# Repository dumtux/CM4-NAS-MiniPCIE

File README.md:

**Rapberry PI compute module 4 NAS PCB for using JLCPCB.com. (pre-test version)**

# General view of PCB based on processing gbr files on JLCPCB.com

Main purpose of design is to make NAS with more reliable SATA connection comparing to USB-to-SATA converters. SATA controllers can be connected through MiniPCIe slot. There are variety of cards in market, mainly my intend was to use this for 2 SATA (see picture below). This is half size card. Cards for 4 SATA with RAID controller also can be connected. 

**Design is made using nighly version of KiCAD 5.99.0**
**Please study Raspberry PI CM4 datasheet**

# Differential lines
*PCB was designed by a newcomer. All steps made are listed below. This section is very important and risky. Mistakes can be made.  90 R and 100R impedance differential lines are used.Calculations of differential lines are made using JLCPCB internal [calculator](https://cart.jlcpcb.com/impedanceCalculation)*

Results of calculation - [90R](https://raw.githubusercontent.com/olvint/CM4-NAS-MiniPCIE/main/PICS/JLCPCB%20Impedance%2090R.png) and [100R](https://raw.githubusercontent.com/olvint/CM4-NAS-MiniPCIE/main/PICS/JLCPCB%20Impedance%20100R.png)

Those results put in KiCAD.

JLC7628 [Stackup](https://cart.jlcpcb.com/impedance) used all settings transfered to [KiCAD stackup](https://raw.githubusercontent.com/olvint/CM4-NAS-MiniPCIE/main/PICS/KiCAD%20Stack.png)

All vias minimal diameter is 0.45 as price will be much higher for VIAs of less size.

# PCB description
## Sockets on PCB
- MiniPCIe slot (designed for hlaf-size cards)
- HDMI in order to use device as media player
- Gigabit LAN
- SD card slot for using CM4’s without eMMC
- USB A 2.0 socket for connecting periphery like Zigbee.
- MicroUSB for installing firmware to CM4 and power supply.
All sockets placed on top edge of PCB for more reliable use and easy design of 3D print case.

## Footprints
All sockets footprints selected to be most common. In standard library of  KiCAD I did not found suitable MicroSD socket. And ofcource footprint of CM4 is also taken from Raspberry PI CM4 IO borad. All external footprints are in folder LIBS.
I wanted to install all sockets on one side of the board and there was not much space. MicroUSB socket I put on other side of the board below MicroSD socket.

## On board connectors.
### Power input. 
There are 2 connectors with 4 pins (GND, +12V, +5V, +3.3V) Connectors can be used for powering board and soldering cable for powering HDDs. 
- +12 V is only used for HDD. Board has 2 interconnected pins, but level +12 V not used on board. MiniPCIe does not have +12V input.
- +5V used for powering CM4 module and giving power to USB and HDMI. Two SMD resettable fuses installed to protect board from short circuit. 
- +3.3 V used for powering PCI-to-SATA module. Nothing else.
- 1.5 V. Special connector made above PCIe slot.  Generaly this level is not required. It is planned to use SATA module based on chip ASM1061 that has [Integrated 3.3V to 1.2V switch regulator](https://www.asmedia.com.tw/eng/e_show_products.php?cate_index=166&item=118). 

Initial CM4 IO Borad has more copmplicated power system with different ICs for protecting not only from short circuit but, under voltage, overload etc.

### GPIO.
Left side of board has GPIO connector and small connector for selecting level of GPIO (GPIO_Vref)
- GPIO 2
- GPIO 3
- GPIO 4
- GPIO 12
- GPIO 15
- GPIO 14

### Service conections and LEDs
There is a connector with following signals
- nRPIBOOT
- PI_POWER_LED
- Global_EN
- nEXTRST
- Analog_P1
- Analog_P0
- RUN_PG
- PI_N_LED

### Other connectors
- USG_OTG connector used to connect USB_OTG_ID pin of CM4 for installing firmware to eMMC. 
- USB hub connecor Connector with 4 pins GND, D+, D-, +5V can be used to connect external USB hub if you need it in your project.
- MiniPCIe USB D+/D-. MiniPCIe slot also has connections for D+ and D- another connector used for it. This is not connected to CM4 D+/D- lines.
- One GND connector just for the case.

### GBR files
GBR files are prepared in [FAB](https://github.com/olvint/CM4-NAS-MiniPCIE/tree/main/FAB) folder. Also archive prepared FAB_JLCPCB.zip for making order. *Please note that you need to turn on option **Impedance** and select JLCPCB7628 stackup*

### KiCAD view
Front

Back

Update 28.12.2020 - Rerouted some tracks. Moved MicroUSB below MicroSD.
Update 02.01.2021 - Rerouted a lot of tracks. Added beauty.

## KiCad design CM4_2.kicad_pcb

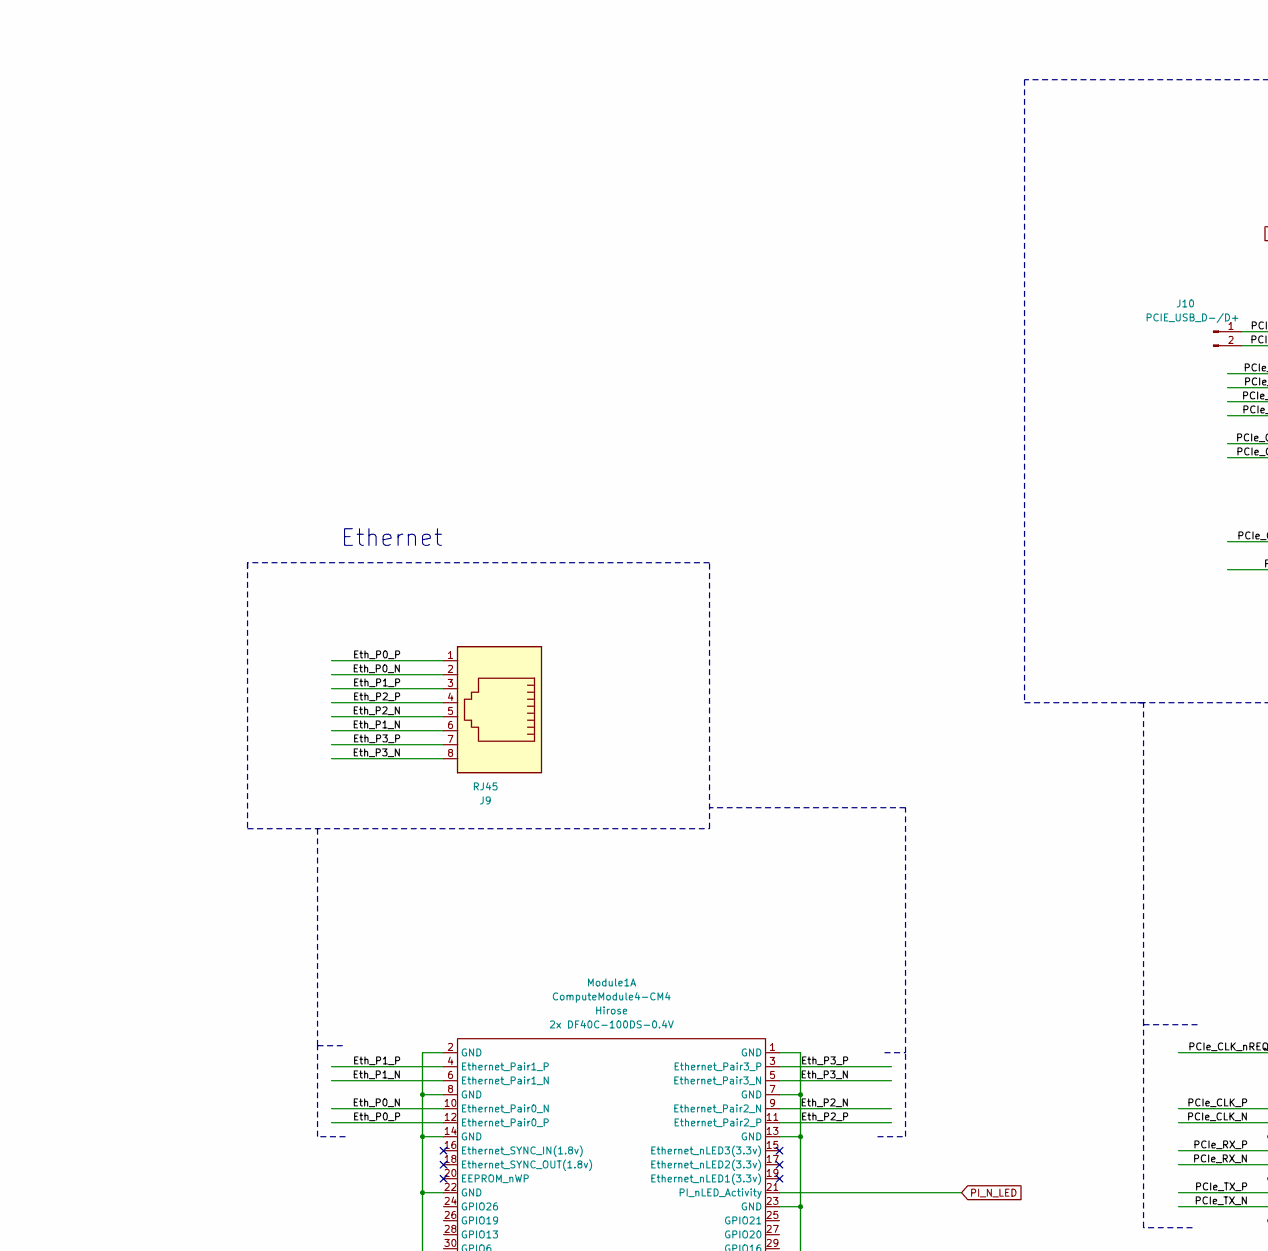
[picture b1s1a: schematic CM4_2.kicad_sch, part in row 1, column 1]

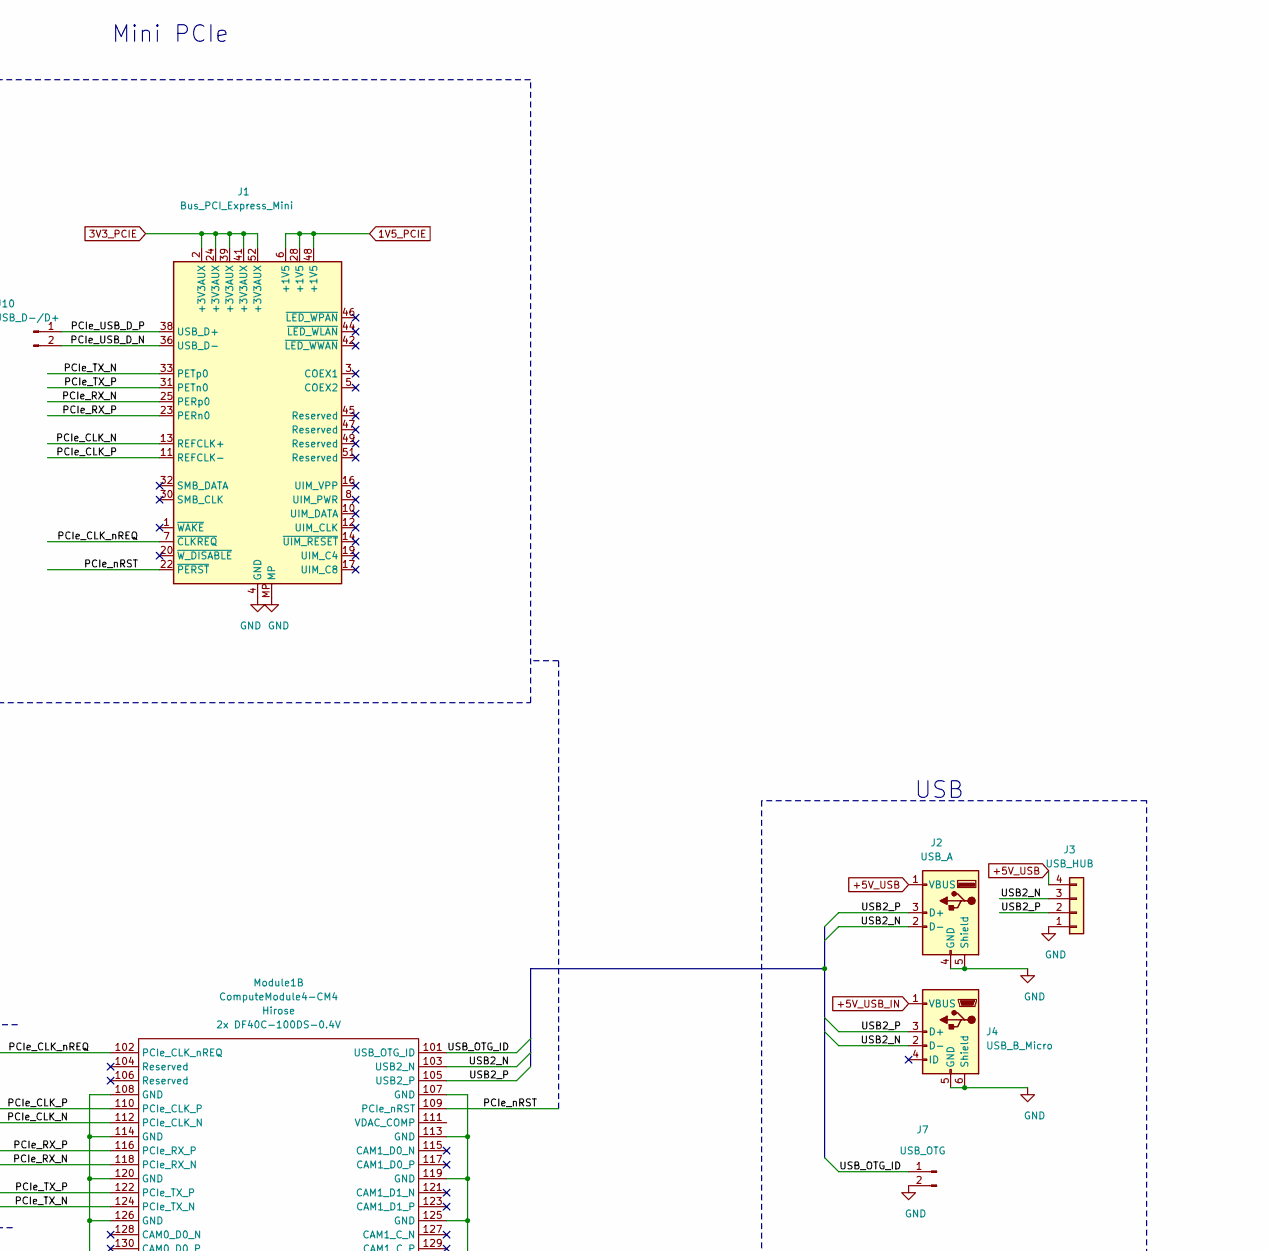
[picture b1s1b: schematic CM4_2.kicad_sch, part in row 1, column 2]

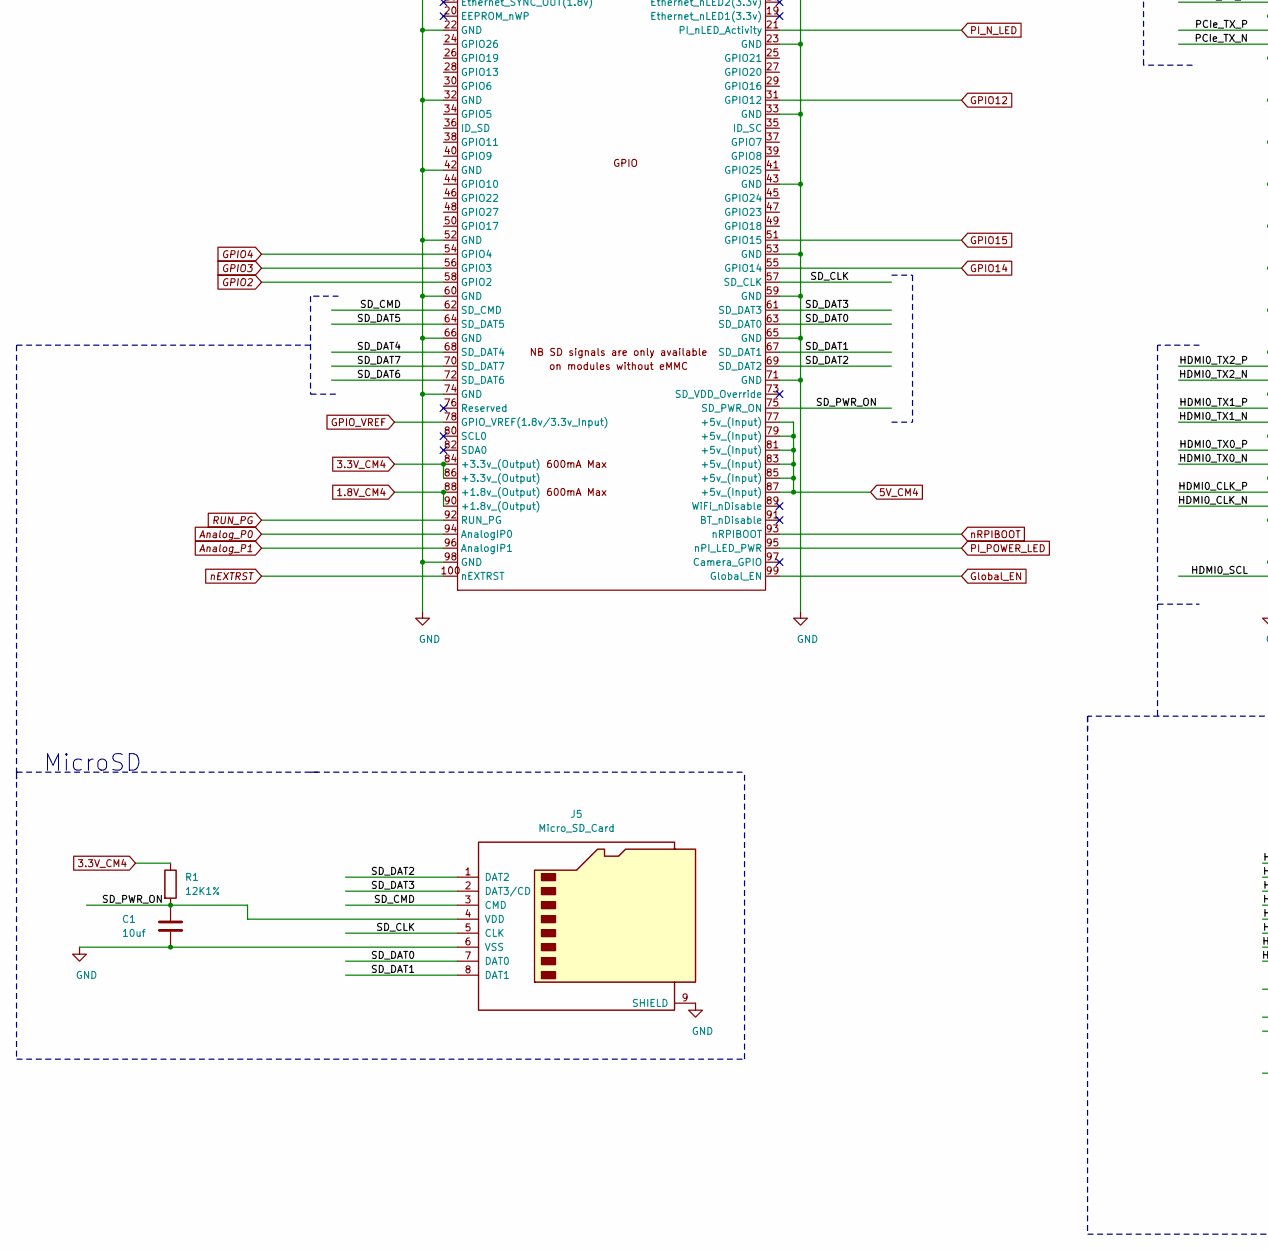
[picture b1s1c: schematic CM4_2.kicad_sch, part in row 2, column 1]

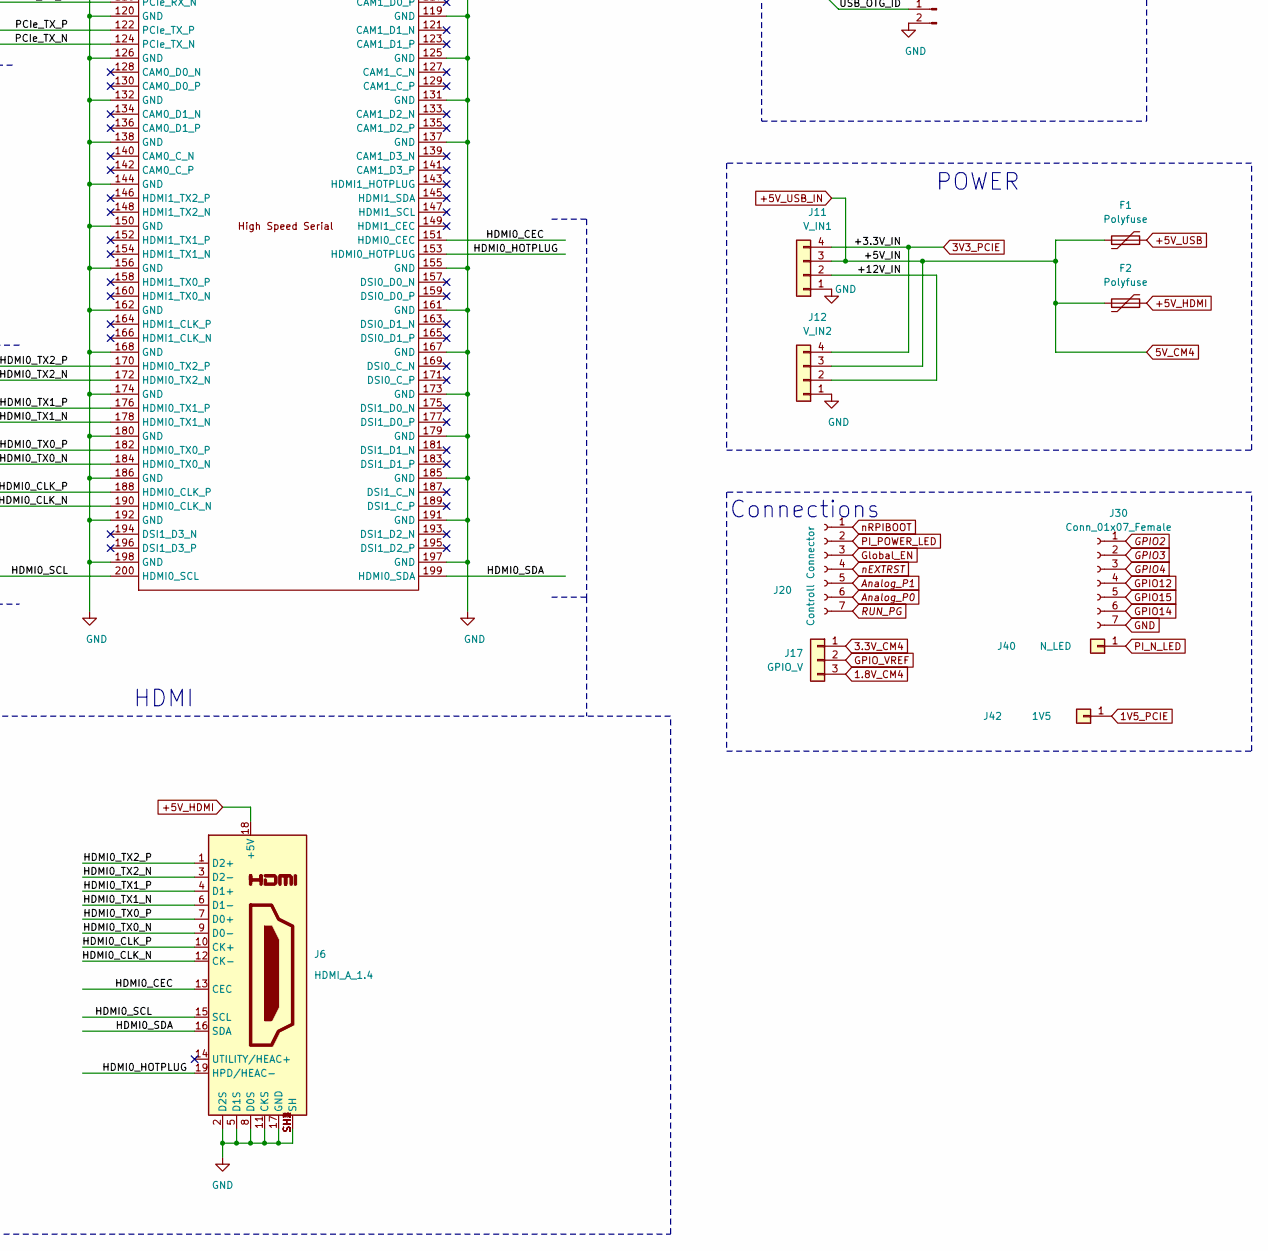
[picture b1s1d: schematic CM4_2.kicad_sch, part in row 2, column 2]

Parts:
C1: 10uf; C_1206_3216Metric
F1, F2: Polyfuse; R_0805_2012Metric
J1: Bus_PCI_Express_Mini; BUS_PCI_Express_Mini_Half
J2: USB_A; USB_A_CONNFLY_DS1095-WNR0
J3: USB_HUB; PinHeader_1x04_P2.54mm_Vertical
J4: USB_B_Micro; USB_Mini-B_Lumberg_2486_01_Horizontal
J5: Micro_SD_Card; Conn_uSDcard
J6: HDMI_A_1.4; EDAC 690-019-298-412
J7: USB_OTG; PinHeader_1x02_P2.54mm_Vertical
J9: RJ45; RJ45_Ninigi_GE
J10: PCIE_USB_D-/D+; PinHeader_1x02_P2.54mm_Vertical
J11: V_IN1; PinHeader_1x04_P2.54mm_Vertical
J12: V_IN2; PinHeader_1x04_P2.54mm_Vertical
J17: GPIO_V; PinHeader_1x03_P2.54mm_Vertical_SMD_Pin1Right
J20: Controll Connector; PinHeader_1x07_P2.54mm_Vertical
J30: Conn_01x07_Female; PinSocket_1x07_P2.54mm_Vertical
J40: N_LED; PinHeader_1x01_P2.54mm_Vertical
J42: 1V5; PinHeader_1x01_P2.54mm_Vertical
Module1: ComputeModule4-CM4; Raspberry-Pi-4-Compute-Module
R1: 12K1%; R_1206_3216Metric

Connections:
1.8V_CM4: J17.3, Module1.88 (+1.8v_(Output)), Module1.90 (+1.8v_(Output))
1V5_PCIE: J1.6 (+1V5), J1.28 (+1V5), J1.48 (+1V5), J42.1
3.3V_CM4: J17.1, Module1.84 (+3.3v_(Output)), Module1.86 (+3.3v_(Output)), R1.1
3V3_PCIE: J1.2 (+3V3AUX), J1.24 (+3V3AUX), J1.39 (+3V3AUX), J1.41 (+3V3AUX), J1.52 (+3V3AUX), J11.4, J12.4
+5V_HDMI: F2.2, J6.18 (+5V)
+5V_USB: F1.2, J2.1 (VBUS), J3.4
+5V_USB_IN: F1.1, F2.1, J4.1 (VBUS), J11.3, J12.3, Module1.77 (+5v_(Input)), Module1.79 (+5v_(Input)), Module1.81 (+5v_(Input)), Module1.83 (+5v_(Input)), Module1.85 (+5v_(Input)), Module1.87 (+5v_(Input))
/+12V_IN: J11.2, J12.2
/Eth_P0_N: J9.2, Module1.10 (Ethernet_Pair0_N)
/Eth_P0_P: J9.1, Module1.12 (Ethernet_Pair0_P)
/Eth_P1_N: J9.6, Module1.6 (Ethernet_Pair1_N)
/Eth_P1_P: J9.3, Module1.4 (Ethernet_Pair1_P)
/Eth_P2_N: J9.5, Module1.9 (Ethernet_Pair2_N)
/Eth_P2_P: J9.4, Module1.11 (Ethernet_Pair2_P)
/Eth_P3_N: J9.8, Module1.5 (Ethernet_Pair3_N)
/Eth_P3_P: J9.7, Module1.3 (Ethernet_Pair3_P)
/HDMI0_CEC: J6.13 (CEC), Module1.151 (HDMI0_CEC)
/HDMI0_CLK_N: J6.12 (CK-), Module1.190 (HDMI0_CLK_N)
/HDMI0_CLK_P: J6.10 (CK+), Module1.188 (HDMI0_CLK_P)
/HDMI0_HOTPLUG: J6.19 (HPD/HEAC-), Module1.153 (HDMI0_HOTPLUG)
/HDMI0_SCL: J6.15 (SCL), Module1.200 (HDMI0_SCL)
/HDMI0_SDA: J6.16 (SDA), Module1.199 (HDMI0_SDA)
/HDMI0_TX0_N: J6.9 (D0-), Module1.184 (HDMI0_TX0_N)
/HDMI0_TX0_P: J6.7 (D0+), Module1.182 (HDMI0_TX0_P)
/HDMI0_TX1_N: J6.6 (D1-), Module1.178 (HDMI0_TX1_N)
/HDMI0_TX1_P: J6.4 (D1+), Module1.176 (HDMI0_TX1_P)
/HDMI0_TX2_N: J6.3 (D2-), Module1.172 (HDMI0_TX2_N)
/HDMI0_TX2_P: J6.1 (D2+), Module1.170 (HDMI0_TX2_P)
/PCIe_CLK_N: J1.13 (REFCLK+), Module1.112 (PCIe_CLK_N)
/PCIe_CLK_P: J1.11 (REFCLK-), Module1.110 (PCIe_CLK_P)
/PCIe_CLK_nREQ: J1.7 (~CLKREQ), Module1.102 (PCIe_CLK_nREQ)
/PCIe_RX_N: J1.25 (PERp0), Module1.118 (PCIe_RX_N)
/PCIe_RX_P: J1.23 (PERn0), Module1.116 (PCIe_RX_P)
/PCIe_TX_N: J1.33 (PETp0), Module1.124 (PCIe_TX_N)
/PCIe_TX_P: J1.31 (PETn0), Module1.122 (PCIe_TX_P)
/PCIe_USB_D_N: J1.36 (USB_D-), J10.2
/PCIe_USB_D_P: J1.38 (USB_D+), J10.1
/PCIe_nRST: J1.22 (~PERST), Module1.109 (PCIe_nRST)
/SD_CLK: J5.5 (CLK), Module1.57 (SD_CLK)
/SD_CMD: J5.3 (CMD), Module1.62 (SD_CMD)
/SD_DAT0: J5.7 (DAT0), Module1.63 (SD_DAT0)
/SD_DAT1: J5.8 (DAT1), Module1.67 (SD_DAT1)
/SD_DAT2: J5.1 (DAT2), Module1.69 (SD_DAT2)
/SD_DAT3: J5.2 (DAT3/CD), Module1.61 (SD_DAT3)
/SD_DAT4: Module1.68 (SD_DAT4)
/SD_DAT5: Module1.64 (SD_DAT5)
/SD_DAT6: Module1.72 (SD_DAT6)
/SD_DAT7: Module1.70 (SD_DAT7)
/SD_PWR_ON: C1.1, J5.4 (VDD), Module1.75 (SD_PWR_ON), R1.2
/USB2_N: J2.2 (D-), J3.3, J4.2 (D-), Module1.103 (USB2_N)
/USB2_P: J2.3 (D+), J3.2, J4.3 (D+), Module1.105 (USB2_P)
/USB_OTG_ID: J7.1, Module1.101 (USB_OTG_ID)
Analog_P0: J20.6, Module1.94 (AnalogIP0)
Analog_P1: J20.5, Module1.96 (AnalogIP1)
GND: C1.2, J1.4 (GND), J1.9 (GND), J1.15 (GND), J1.18 (GND), J1.21 (GND), J1.26 (GND), J1.27 (GND), J1.29 (GND), J1.34 (GND), J1.35 (GND), J1.37 (GND), J1.40 (GND), J1.43 (GND), J1.50 (GND), J1.MP, J2.4 (GND), J2.5 (Shield), J3.1, J4.5 (GND), J4.6 (Shield), J5.6 (VSS), J5.9 (SHIELD), J6.2 (D2S), J6.5 (D1S), J6.8 (D0S), J6.11 (CKS), J6.17 (GND), J6.SH1 (SH), J6.SH2 (SH), J6.SH3 (SH), J6.SH4 (SH), J7.2, J11.1, J12.1, J30.7, Module1.1 (GND), Module1.2 (GND), Module1.7 (GND), Module1.8 (GND), Module1.13 (GND), Module1.14 (GND), Module1.22 (GND), Module1.23 (GND), Module1.32 (GND), Module1.33 (GND), Module1.42 (GND), Module1.43 (GND), Module1.52 (GND), Module1.53 (GND), Module1.59 (GND), Module1.60 (GND), Module1.65 (GND), Module1.66 (GND), Module1.71 (GND), Module1.74 (GND), Module1.98 (GND), Module1.107 (GND), Module1.108 (GND), Module1.113 (GND), Module1.114 (GND), Module1.119 (GND), Module1.120 (GND), Module1.125 (GND), Module1.126 (GND), Module1.131 (GND), Module1.132 (GND), Module1.137 (GND), Module1.138 (GND), Module1.144 (GND), Module1.150 (GND), Module1.155 (GND), Module1.156 (GND), Module1.161 (GND), Module1.162 (GND), Module1.167 (GND), Module1.168 (GND), Module1.173 (GND), Module1.174 (GND), Module1.179 (GND), Module1.180 (GND), Module1.185 (GND), Module1.186 (GND), Module1.191 (GND), Module1.192 (GND), Module1.197 (GND), Module1.198 (GND)
GPIO2: J30.1, Module1.58 (GPIO2)
GPIO3: J30.2, Module1.56 (GPIO3)
GPIO4: J30.3, Module1.54 (GPIO4)
GPIO12: J30.4, Module1.31 (GPIO12)
GPIO14: J30.6, Module1.55 (GPIO14)
GPIO15: J30.5, Module1.51 (GPIO15)
GPIO_VREF: J17.2, Module1.78 (GPIO_VREF(1.8v/3.3v_Input))
Global_EN: J20.3, Module1.99 (Global_EN)
PI_N_LED: J40.1, Module1.21 (PI_nLED_Activity)
PI_POWER_LED: J20.2, Module1.95 (nPI_LED_PWR)
RUN_PG: J20.7, Module1.92 (RUN_PG)
nEXTRST: J20.4, Module1.100 (nEXTRST)
nRPIBOOT: J20.1, Module1.93 (nRPIBOOT)
no_connect_92: J1.1 (~WAKE)
no_connect_93: J1.10 (UIM_DATA)
no_connect_94: J1.12 (UIM_CLK)
no_connect_95: J1.14 (~UIM_RESET)
no_connect_96: J1.16 (UIM_VPP)
no_connect_97: J1.17 (UIM_C8)
no_connect_98: J1.19 (UIM_C4)
no_connect_99: J1.20 (~W_DISABLE)
no_connect_100: J1.3 (COEX1)
no_connect_101: J1.30 (SMB_CLK)
no_connect_102: J1.32 (SMB_DATA)
no_connect_103: J1.42 (~LED_WWAN)
no_connect_104: J1.44 (~LED_WLAN)
no_connect_105: J1.45 (Reserved)
no_connect_106: J1.46 (~LED_WPAN)
no_connect_107: J1.47 (Reserved)
no_connect_108: J1.49 (Reserved)
no_connect_109: J1.5 (COEX2)
no_connect_110: J1.51 (Reserved)
no_connect_111: J1.8 (UIM_PWR)
no_connect_112: J4.4 (ID)
no_connect_113: J6.14 (UTILITY/HEAC+)
no_connect_114: Module1.104 (Reserved)
no_connect_115: Module1.106 (Reserved)
no_connect_116: Module1.115 (CAM1_D0_N)
no_connect_117: Module1.117 (CAM1_D0_P)
no_connect_118: Module1.121 (CAM1_D1_N)
no_connect_119: Module1.123 (CAM1_D1_P)
no_connect_120: Module1.127 (CAM1_C_N)
no_connect_121: Module1.128 (CAM0_D0_N)
no_connect_122: Module1.129 (CAM1_C_P)
no_connect_123: Module1.130 (CAM0_D0_P)
no_connect_124: Module1.133 (CAM1_D2_N)
no_connect_125: Module1.134 (CAM0_D1_N)
no_connect_126: Module1.135 (CAM1_D2_P)
no_connect_127: Module1.136 (CAM0_D1_P)
no_connect_128: Module1.139 (CAM1_D3_N)
no_connect_129: Module1.140 (CAM0_C_N)
no_connect_130: Module1.141 (CAM1_D3_P)
no_connect_131: Module1.142 (CAM0_C_P)
no_connect_132: Module1.143 (HDMI1_HOTPLUG)
no_connect_133: Module1.145 (HDMI1_SDA)
no_connect_134: Module1.146 (HDMI1_TX2_P)
no_connect_135: Module1.147 (HDMI1_SCL)
no_connect_136: Module1.148 (HDMI1_TX2_N)
no_connect_137: Module1.149 (HDMI1_CEC)
no_connect_138: Module1.15 (Ethernet_nLED3(3.3v))
no_connect_139: Module1.152 (HDMI1_TX1_P)
no_connect_140: Module1.154 (HDMI1_TX1_N)
no_connect_141: Module1.157 (DSI0_D0_N)
no_connect_142: Module1.158 (HDMI1_TX0_P)
no_connect_143: Module1.159 (DSI0_D0_P)
no_connect_144: Module1.16 (Ethernet_SYNC_IN(1.8v))
no_connect_145: Module1.160 (HDMI1_TX0_N)
no_connect_146: Module1.163 (DSI0_D1_N)
no_connect_147: Module1.164 (HDMI1_CLK_P)
no_connect_148: Module1.165 (DSI0_D1_P)
no_connect_149: Module1.166 (HDMI1_CLK_N)
no_connect_150: Module1.169 (DSI0_C_N)
no_connect_151: Module1.17 (Ethernet_nLED2(3.3v))
no_connect_152: Module1.171 (DSI0_C_P)
no_connect_153: Module1.175 (DSI1_D0_N)
no_connect_154: Module1.177 (DSI1_D0_P)
no_connect_155: Module1.18 (Ethernet_SYNC_OUT(1.8v))
no_connect_156: Module1.181 (DSI1_D1_N)
no_connect_157: Module1.183 (DSI1_D1_P)
no_connect_158: Module1.187 (DSI1_C_N)
no_connect_159: Module1.189 (DSI1_C_P)
no_connect_160: Module1.19 (Ethernet_nLED1(3.3v))
no_connect_161: Module1.193 (DSI1_D2_N)
no_connect_162: Module1.194 (DSI1_D3_N)
no_connect_163: Module1.195 (DSI1_D2_P)
no_connect_164: Module1.196 (DSI1_D3_P)
no_connect_165: Module1.20 (EEPROM_nWP)
no_connect_166: Module1.73 (SD_VDD_Override)
no_connect_167: Module1.76 (Reserved)
no_connect_168: Module1.80 (SCL0)
no_connect_169: Module1.82 (SDA0)
no_connect_170: Module1.89 (WiFi_nDisable)
no_connect_171: Module1.91 (BT_nDisable)
no_connect_172: Module1.97 (Camera_GPIO)

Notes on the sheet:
MicroSD
Ethernet
HDMI
Mini PCIe
Connections
USB
POWER

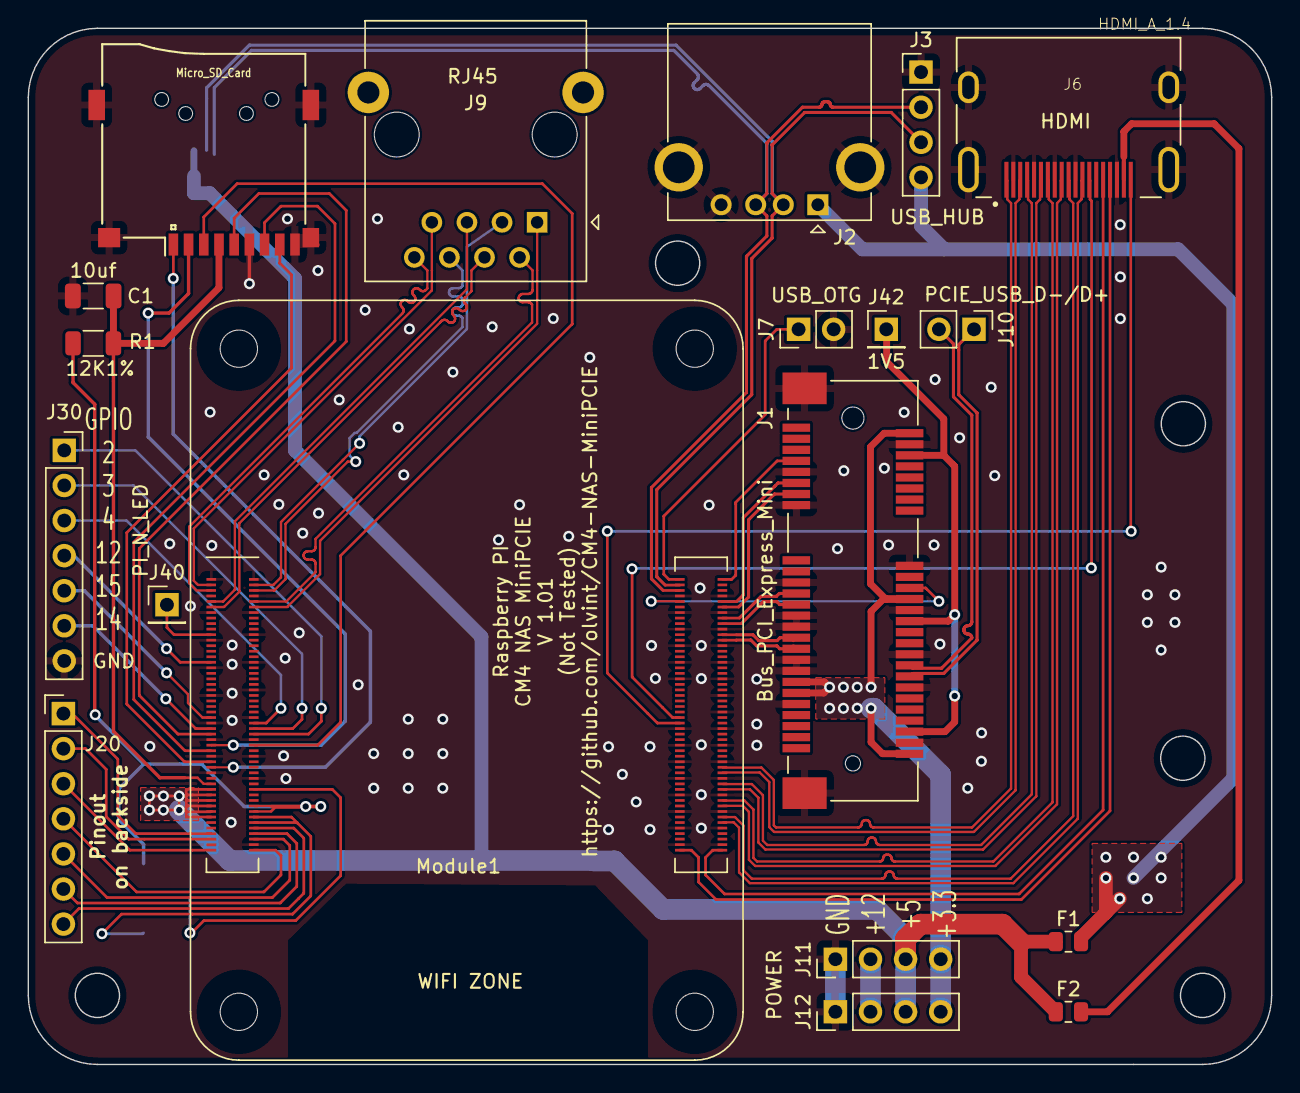
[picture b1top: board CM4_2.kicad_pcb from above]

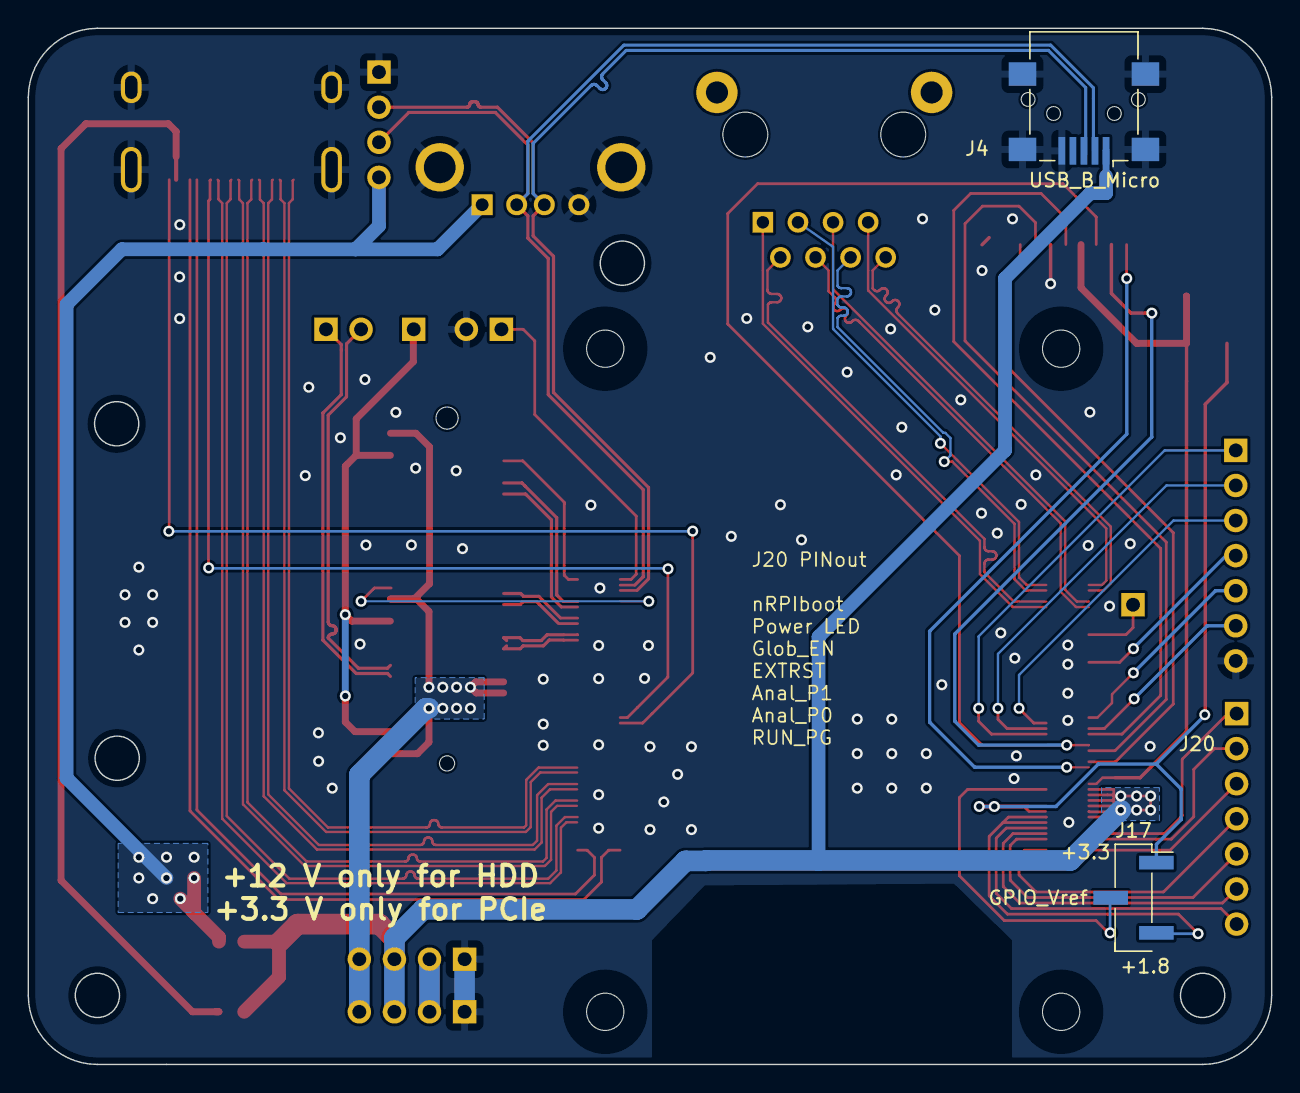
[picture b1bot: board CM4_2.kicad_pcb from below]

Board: 4 copper layers, 90.0 x 75.0 mm, 21 parts (2 on the bottom side), 64 nets.

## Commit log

2020-12-28 Some tracks rerouted, MicroUSB moved
2020-12-28 Minor move
2020-12-28 R2 to R1, C2 to C1
2020-12-29 Minor
2021-01-02 v1.01
2021-01-02 Drill Holes
